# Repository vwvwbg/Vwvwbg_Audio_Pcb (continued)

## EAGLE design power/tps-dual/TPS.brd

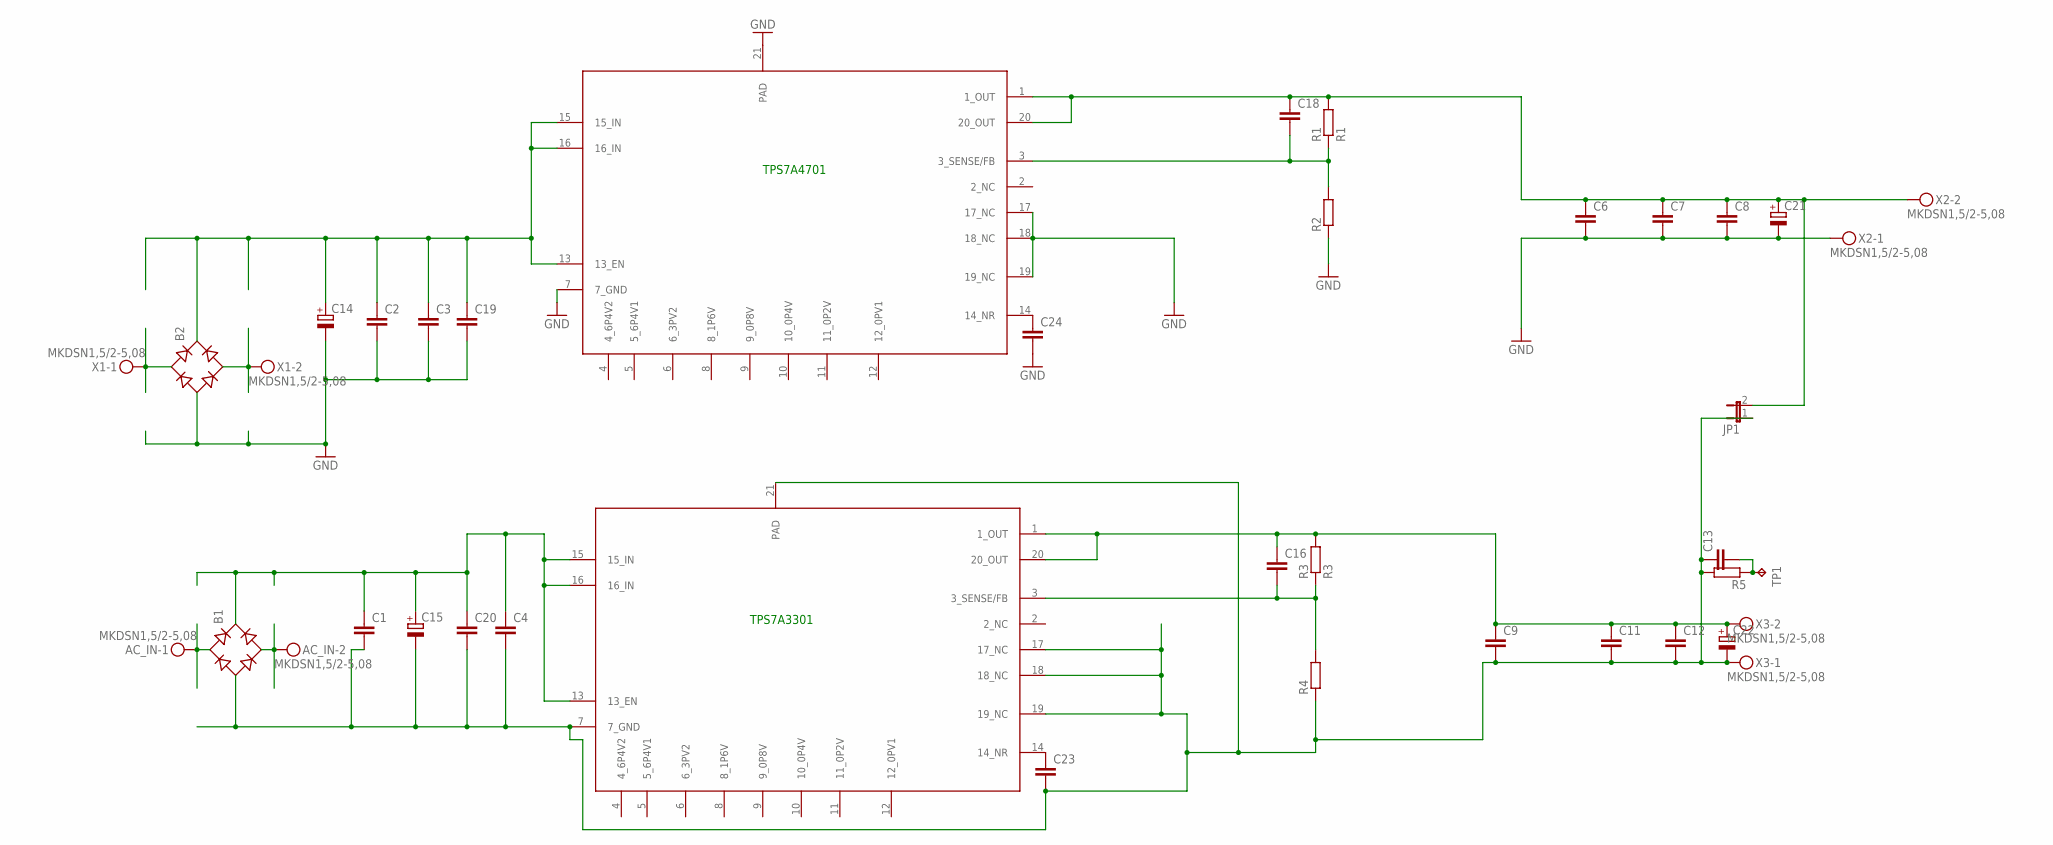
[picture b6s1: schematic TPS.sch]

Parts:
AC_IN: MKDSN1,5/2-5,08
B1, B2: RB1A
C1, C2, C8, C11: C-EUC1210; C1210
C3, C4, C7, C12: C-EUC0805; C0805
C6, C9, C16, C18, C19, C20, C23, C24: C-EUC0603; C0603
C13: C-EU075-042X103; C075-042X103
C14, C15: CPOL-EUE5-13; E5-13
C21, C22: CPOL-EUE3.5-8; E3,5-8
JP1: JP1E; JP1
R1: R1; R0805
R2, R4: R-EU_R0805; R0805
R3: R3; R0805
R5: R-EU_0207/12; 0207/12
TP1: TPPAD1-13; P1-13
U$1, U$2: TPS7A4701; QFN65P500X500X100-21N
X1, X2, X3: MKDSN1,5/2-5,08

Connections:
GND: B2.-, C2.2, C3.2, C6.2, C7.2, C8.2, C14.-, C19.2, C21.-, C24.2, R2.1, U$1.7 (7_GND), U$1.17 (17_NC), U$1.18 (18_NC), U$1.19 (19_NC), U$1.21 (PAD), X2.1
GND2: B1.-, C1.2, C4.2, C9.2, C11.2, C12.2, C13.1, C15.-, C20.2, C22.-, C23.2, JP1.1, R4.1, R5.2, U$2.7 (7_GND), U$2.17 (17_NC), U$2.18 (18_NC), U$2.19 (19_NC), U$2.21 (PAD), X3.1
unnamed: AC_IN.1, B1.AC1
unnamed: B2.+, C2.1, C3.1, C14.+, C19.1, U$1.13 (13_EN), U$1.15 (15_IN), U$1.16 (16_IN)
unnamed: C23.1, U$2.14 (14_NR)
unnamed: C16.2, R3.1, R4.2, U$2.3 (3_SENSE/FB)
unnamed: C24.1, U$1.14 (14_NR)
unnamed: B2.AC2, X1.2
unnamed: B2.AC1, X1.1
unnamed: AC_IN.2, B1.AC2
unnamed: C13.2, R5.1, TP1.TP
unnamed: B1.+, C1.1, C4.1, C15.+, C20.1, U$2.13 (13_EN), U$2.15 (15_IN), U$2.16 (16_IN)
unnamed: C18.2, R1.1, R2.2, U$1.3 (3_SENSE/FB)
V+: C6.1, C7.1, C8.1, C18.1, C21.+, JP1.2, R1.2, U$1.1 (1_OUT), U$1.20 (20_OUT), X2.2
V-: C9.1, C11.1, C12.1, C16.1, C22.+, R3.2, U$2.1 (1_OUT), U$2.20 (20_OUT), X3.2

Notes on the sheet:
TPS7A4701
TPS7A3301

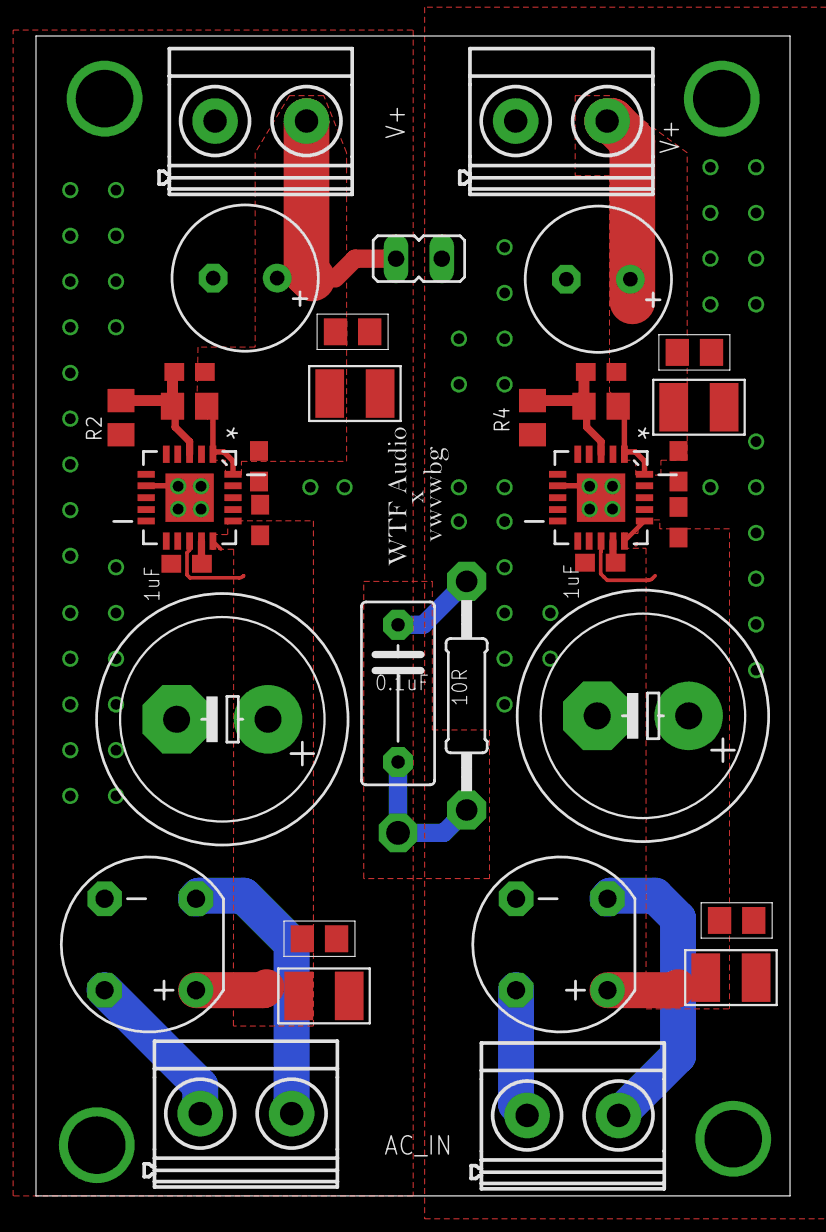
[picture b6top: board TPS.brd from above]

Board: 2 copper layers, 41.9 x 64.4 mm, 36 parts (0 on the bottom side), 15 nets.

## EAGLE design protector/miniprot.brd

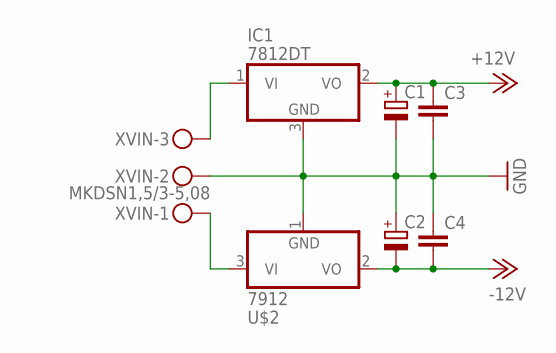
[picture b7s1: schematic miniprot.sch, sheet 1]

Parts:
C1, C2: CPOL-EUE2.5-7; E2,5-7
C3, C4: C-EUC0805; C0805
IC1: 7812DT; TO252
U$2: 7912; TO252
XVIN: MKDSN1,5/3-5,08

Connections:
+12V: C1.+, C3.1, IC1.2 (VO); also elsewhere on the board
-12V: C2.-, C4.2, U$2.2 (VO); also elsewhere on the board
GND: C1.-, C2.+, C3.2, C4.1, IC1.3 (GND), U$2.1 (GND), XVIN.2; also elsewhere on the board
unnamed: IC1.1 (VI), XVIN.3
unnamed: U$2.3 (VI), XVIN.1

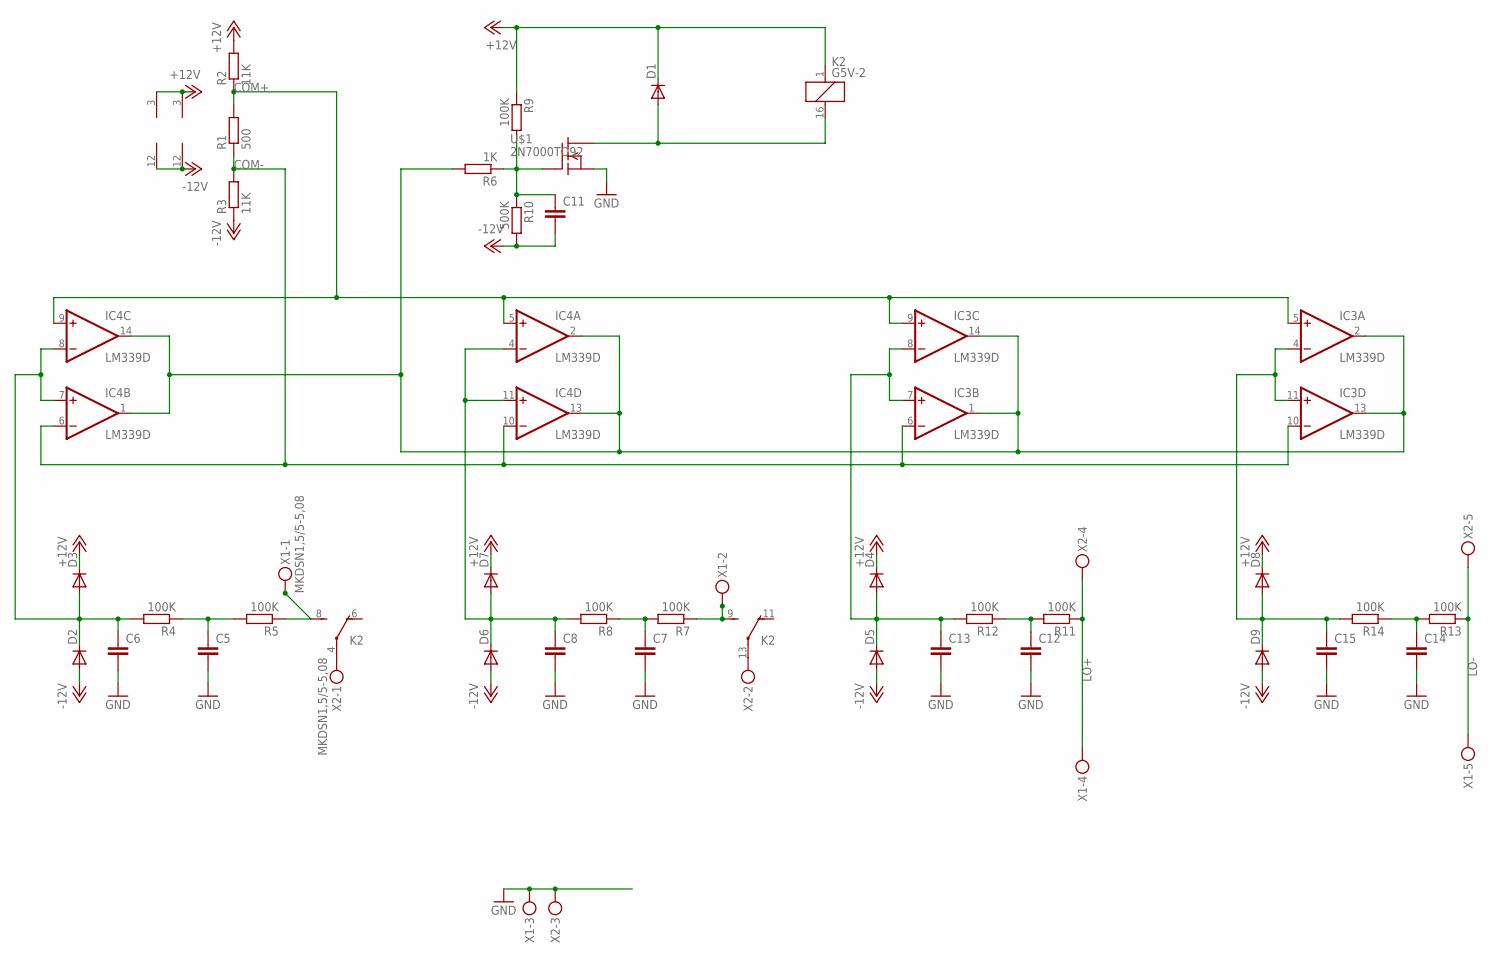
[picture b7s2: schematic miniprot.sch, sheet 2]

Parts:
C5, C6, C7, C8, C12, C13, C14, C15: C-EUC0805; C0805
C11: C-EUC1210; C1210
D1: DIODE-DO214AC; DO214AC
D2, D3, D4, D5, D6, D7, D8, D9: DIODE-SOD80C; SOD80C
IC3, IC4: LM339D; SO14
K2: G5V-2
R1: 500; R0805
R2, R3: 11K; R0805
R4, R5, R7, R8, R9, R11, R12, R13, R14: 100K; R0805
R6: 1K; R0805
R10: 500K; R0805
U$1: 2N7000TO92; TO92-
X1, X2: MKDSN1,5/5-5,08

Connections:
+12V: D1.C, D3.C, D4.C, D7.C, D8.C, IC3.3 (V+), IC4.3 (V+), K2.1, R2.2, R9.1; also elsewhere on the board
-12V: C11.2, D2.A, D5.A, D6.A, D9.A, IC3.12 (GND), IC4.12 (GND), R3.1, R10.2; also elsewhere on the board
COM+: IC3.5 (+IN), IC3.9 (+IN), IC4.5 (+IN), IC4.9 (+IN), R1.2, R2.1
COM-: IC3.6 (-IN), IC3.10 (-IN), IC4.6 (-IN), IC4.10 (-IN), R1.1, R3.2
GND: C5.2, C6.2, C7.2, C8.2, C12.2, C13.2, C14.2, C15.2, U$1.3 (S), X1.3, X2.3; also elsewhere on the board
LO+: R11.1, X1.4, X2.4
LO-: R13.1, X1.5, X2.5
unnamed: IC3.1 (OUT), IC3.2 (OUT), IC3.13 (OUT), IC3.14 (OUT), IC4.1 (OUT), IC4.2 (OUT), IC4.13 (OUT), IC4.14 (OUT), R6.2
unnamed: K2.8 (S), R5.1, X1.1
unnamed: C7.1, R7.2, R8.1
unnamed: C5.1, R4.1, R5.2
unnamed: K2.9 (S), R7.1, X1.2
unnamed: K2.13, X2.2
unnamed: C11.1, R6.1, R9.2, R10.1, U$1.2 (G)
unnamed: C6.1, D2.C, D3.A, IC4.7 (+IN), IC4.8 (-IN), R4.2
unnamed: C8.1, D6.C, D7.A, IC4.4 (-IN), IC4.11 (+IN), R8.2
unnamed: D1.A, K2.16 (2), U$1.1 (D)
unnamed: C13.1, D4.A, D5.C, IC3.7 (+IN), IC3.8 (-IN), R12.2
unnamed: C15.1, D8.A, D9.C, IC3.4 (-IN), IC3.11 (+IN), R14.2
unnamed: K2.4, X2.1
unnamed: C12.1, R11.2, R12.1
unnamed: C14.1, R13.2, R14.1

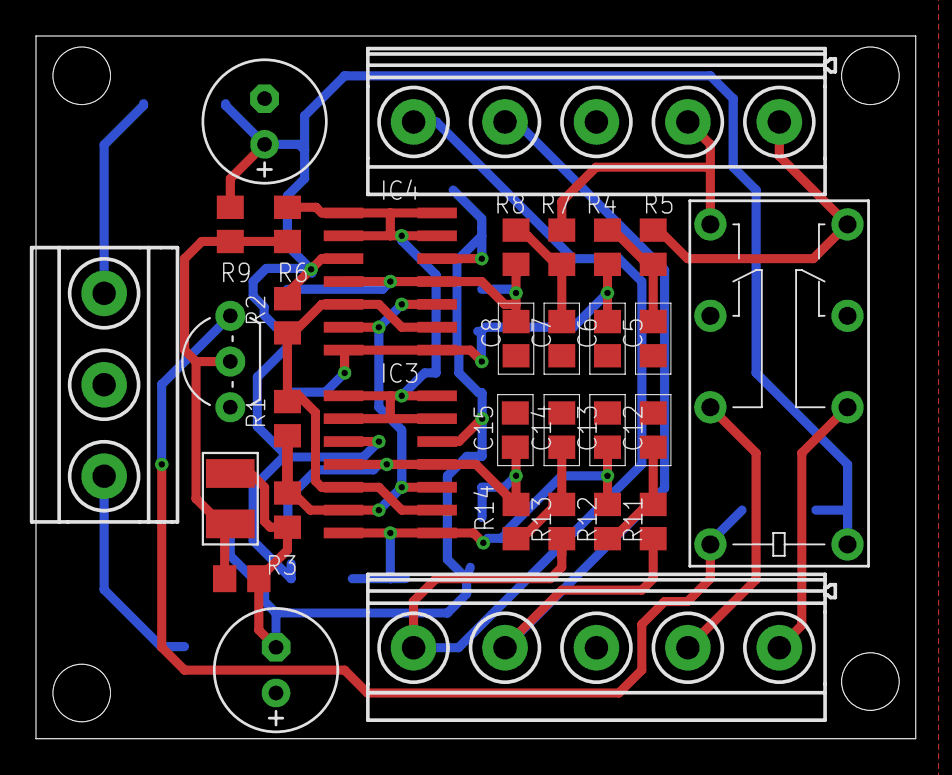
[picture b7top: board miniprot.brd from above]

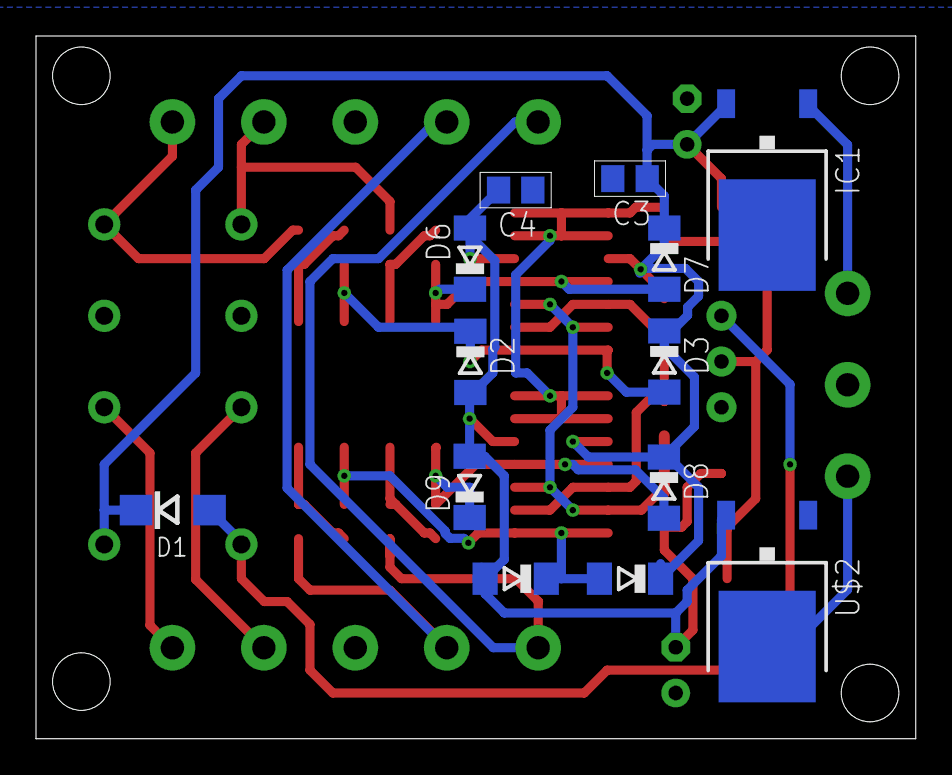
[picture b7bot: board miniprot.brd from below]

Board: 2 copper layers, 48.9 x 39.0 mm, 45 parts (13 on the bottom side), 24 nets.
